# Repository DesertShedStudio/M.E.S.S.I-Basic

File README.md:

M.E.S.S.I Basic
============

The "M.E.S.S.I Basic" is an open source OSHWA Certified hardware design, implementing a RS-422 interface for use with Mesa Ethernet Anything 
I/O Cards and Mesa Electronics smart serial daughter cards.

M.E.S.S.I <br>
"Mesa Electronics Smart Serial Interface"

This repository is aimed towards those who wish to manufacture their own boards. 

Board Rendering
============

License
=======

M.E.S.S.I Basic | https://github.com/DesertShedStudio/M.E.S.S.I-Basic <br>
Copyright (c) Desert Shed Studio

This source describes Open Hardware and is licensed under the CERN-OHL-S v2.

You may redistribute and modify this source and make products using it under <br>
the terms of the CERN-OHL-S v2 (https://ohwr.org/cern_ohl_s_v2.txt). <br>

This source is distributed WITHOUT ANY EXPRESS OR IMPLIED WARRANTY, <br>
INCLUDING OF MERCHANTABILITY, SATISFACTORY QUALITY AND FITNESS FOR A <br>
PARTICULAR PURPOSE. Please see the CERN-OHL-S v2 for applicable conditions.

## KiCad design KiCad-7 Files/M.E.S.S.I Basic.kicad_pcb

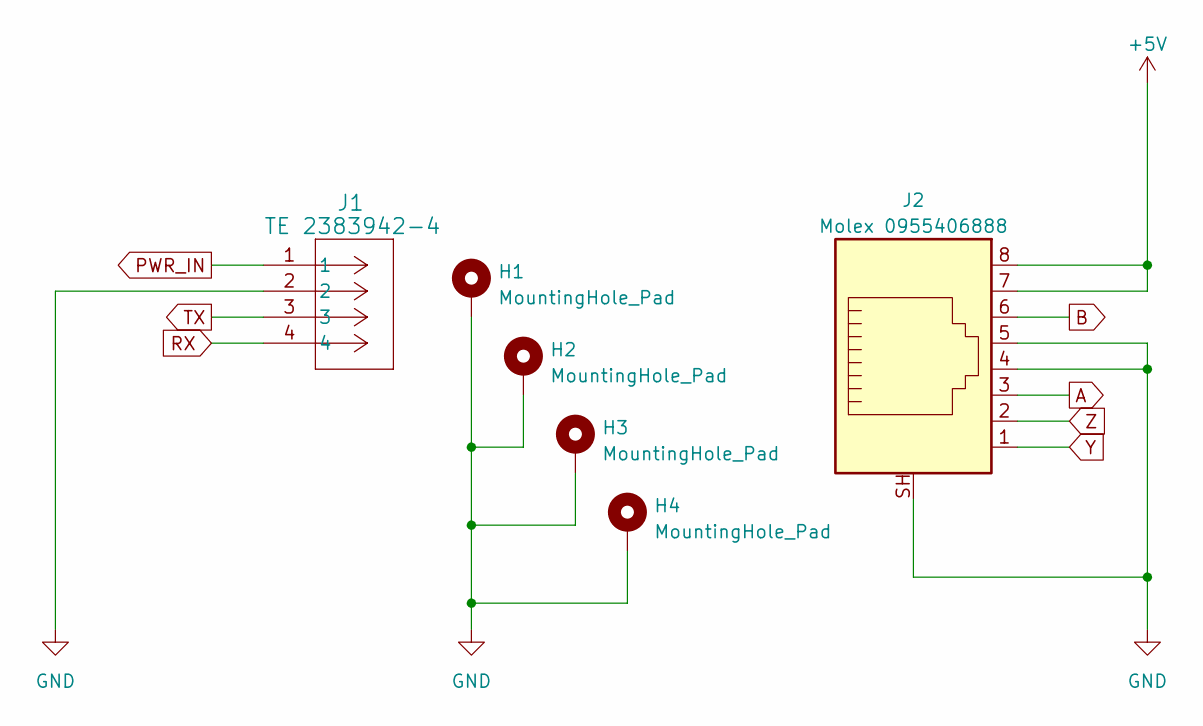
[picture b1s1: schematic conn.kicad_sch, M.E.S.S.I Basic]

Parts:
H1, H2, H3, H4: MountingHole_Pad; MountingHole_2.7mm_M2.5_Pad_Via
J1: TE 2383942-4; TE_23823942-4
J2: Molex 0955406888; Molex_0955406888

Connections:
+5V: J2.7, J2.8; also elsewhere on the board
A: J2.3; also elsewhere on the board
B: J2.6; also elsewhere on the board
GND: H1.1, H2.1, H3.1, H4.1, J1.2, J2.4, J2.5, J2.SH; also elsewhere on the board
PWR_IN: J1.1; also elsewhere on the board
RX: J1.4; also elsewhere on the board
TX: J1.3; also elsewhere on the board
Y: J2.1; also elsewhere on the board
Z: J2.2; also elsewhere on the board

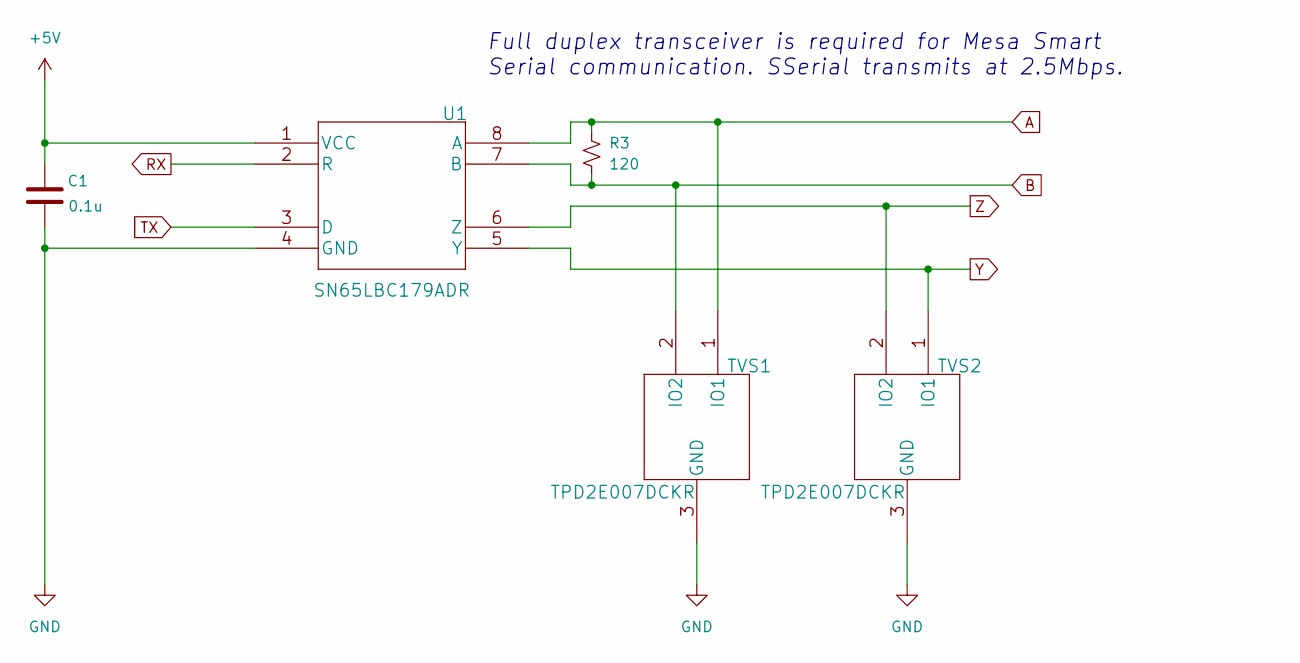
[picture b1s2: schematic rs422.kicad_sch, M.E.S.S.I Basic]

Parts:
C1: 0.1u; C_0603_1608Metric
R3: 120; R_0603_1608Metric
TVS1, TVS2: TPD2E007DCKR; SOT-323_SC-70
U1: SN65LBC179ADR; SOIC-8_3.9x4.9mm_P1.27mm

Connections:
+5V: C1.2, U1.1 (VCC); also elsewhere on the board
A: R3.1, TVS1.1 (IO1), U1.8 (A); also elsewhere on the board
B: R3.2, TVS1.2 (IO2), U1.7 (B); also elsewhere on the board
GND: C1.1, TVS1.3 (GND), TVS2.3 (GND), U1.4 (GND); also elsewhere on the board
RX: U1.2 (R); also elsewhere on the board
TX: U1.3 (D); also elsewhere on the board
Y: TVS2.1 (IO1), U1.5 (Y); also elsewhere on the board
Z: TVS2.2 (IO2), U1.6 (Z); also elsewhere on the board

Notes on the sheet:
Full duplex transceiver is required for Mesa Smart Serial communication. SSerial transmits at 2.5Mbps.

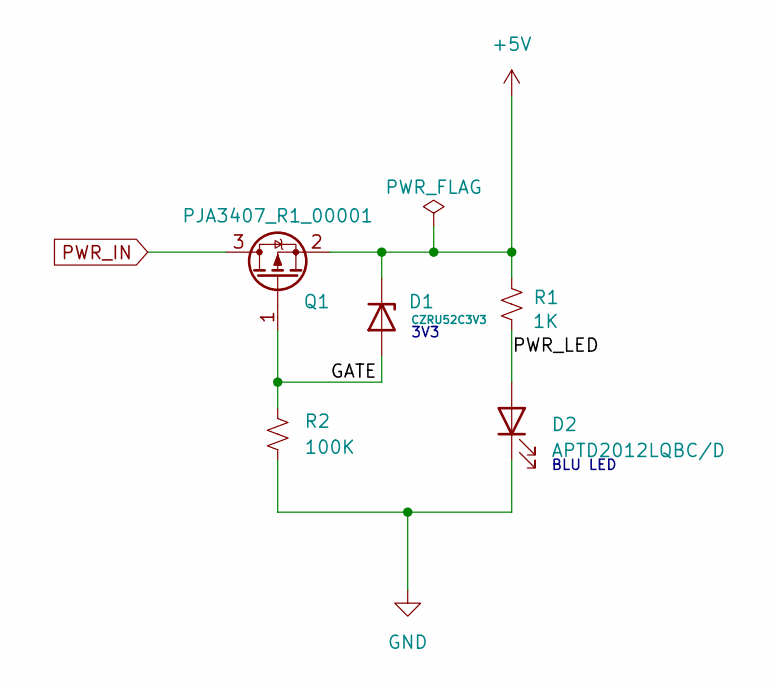
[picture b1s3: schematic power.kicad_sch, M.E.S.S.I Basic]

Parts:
D1: CZRU52C3V3; D_0603_1608Metric
D2: APTD2012LQBC/D; LED_0805_2012Metric
Q1: PJA3407_R1_00001; SOT-23
R1: 1K; R_0603_1608Metric
R2: 100K; R_0603_1608Metric

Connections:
+5V: D1.1 (K), Q1.2 (S), R1.1; also elsewhere on the board
/Power/GATE: D1.2 (A), Q1.1 (G), R2.1
/Power/PWR_LED: D2.2 (A), R1.2
GND: D2.1 (K), R2.2; also elsewhere on the board
PWR_IN: Q1.3 (D); also elsewhere on the board

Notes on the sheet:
3V3
BLU LED

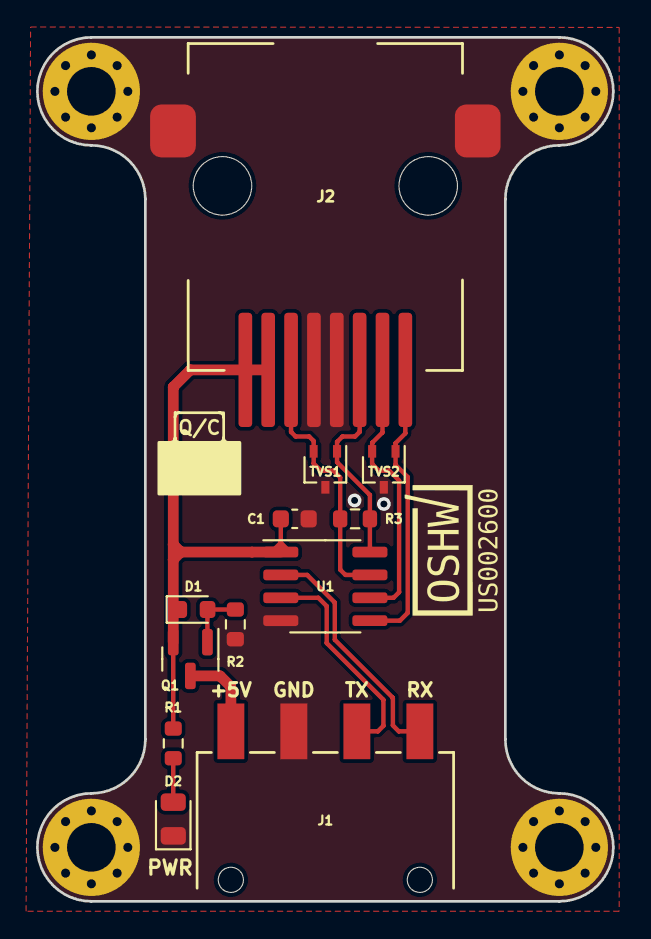
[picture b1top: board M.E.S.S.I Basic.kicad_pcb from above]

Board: 2 copper layers, 32.0 x 48.0 mm, 16 parts (0 on the bottom side), 11 nets.

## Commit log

2024-01-20 Update README.md
    Added license and description.
2024-01-20 Update README.md
    Correction to formatting.
2024-01-20 Add files via upload
    Initial upload of M.E.S.S.I Basic source files.
2024-01-20 Update README.md
    Fixed board rendering url.
2024-01-20 Update README.md
    fixed board rendering url formatting.
2024-01-20 Update and rename CHANGES.txt.txt to CHANGES.txt
    corrected file name.
2024-01-21 Rename M.E.S.S.I Basic.pdf to M.E.S.S.I Basic Schematic.pdf
    Updated name to reflect file contents.
2024-01-21 Add files via upload
    Added pdf file for BOM.
2024-01-21 Update README.md
    spelling correction.
2024-01-21 Add files via upload
    Added SN65LBC179ADR Data Sheet.
2024-01-23 Delete Images/00.jpg
    delete old 00.jpg
2024-01-23 Add files via upload
    upload new 00 jpg and certification-mark png
2024-01-23 Add files via upload
    upload new gerbers with certification mark.
2024-01-23 Add files via upload
    upload new kicad 7 files with certification mark
2024-01-23 Add files via upload
    add svg format for certification mark.
2024-01-23 Update README.md
    update to reflect OSHWA certification.
